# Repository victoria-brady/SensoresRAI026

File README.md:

# SensoresRAI026 — Array de sensores de proximidad para RAI

Firmware y herramientas del **array de sensores de distancia** del robot perro
cuadrúpedo **RAI** (ITBA, RAI 2026).

El sistema lee **4 sensores láser ToF VL53L0X** + **2 sensores ultrasónicos
HC-SR04** sobre un **Arduino GIGA R1 WiFi**, filtra las lecturas y emite las
distancias (en mm) por **USB Serial**. Una PC con el Arduino enchufado corre un
puente Python que reenvía esos datos por **UDP** al *brainstem* del robot, que
los usa para el reflejo de detección/frenado ante obstáculos.

```
   ┌──────────────┐   USB Serial    ┌─────────────────────────┐    UDP :43899   ┌────────────┐
   │ Arduino GIGA │  115200 baud    │ PC con el Arduino:       │   datagramas    │ brainstem  │
   │  R1 WiFi     │ ───────────────▶│ serial_to_udp_bridge.py │ ───────────────▶│ del robot  │
   │ (firmware)   │  CSV de 6 dist. │ (lee Serial, manda UDP) │                 │            │
   └──────────────┘                 └─────────────────────────┘                 └────────────┘
        ▲
   4× VL53L0X (I2C) + 2× HC-SR04 (interrupción)
```

---

## Versión activa

> **La versión activa y de referencia es [`src/object_detect_V3/`](src/object_detect_V3/).**

Es la última iteración (junio 2026) y la única con arquitectura **modular**
(drivers, filtro, scheduler y empaquetado en archivos separados). Las versiones
anteriores se conservan como histórico — ver [Historial de versiones](#historial-de-versiones).

> ⚠️ **Gap conocido de integración.** El firmware V3 emite el CSV *sin* el marco
> `S...E`, pero el puente `serial_to_udp_bridge.py` todavía descarta toda línea
> que no empiece con `S` y termine con `E` (protocolo de la V2). Tal cual están
> hoy, **V3 + bridge no se hablan**: el bridge filtra el 100% de los paquetes.
> Ver [Integración Serial → UDP](#integración-serial--udp).

---

## Hardware

| Componente            | Cantidad | Bus / Pines                                  |
|-----------------------|----------|----------------------------------------------|
| Arduino GIGA R1 WiFi  | 1        | Placa principal                              |
| VL53L0X (láser ToF)   | 4        | I2C @ 400 kHz · XSHUT en D2, D3, D4, D5      |
| HC-SR04 (ultrasónico) | 2        | TRIG D8 / ECHO D9 · TRIG D13 / ECHO D12      |

- Cada VL53L0X recibe una dirección I2C única en el arranque (`0x30`–`0x33`),
  encendiéndolos de a uno por su pin XSHUT.
- Los HC-SR04 se miden por **interrupción** sobre el pin ECHO (CHANGE), así el
  loop nunca se bloquea esperando el eco.
- El diseño de la placa (KiCad, 6 sensores) está en [`PCB/`](PCB/).

---

## Estructura del repositorio

```
src/
  object_detect_V3/        ← VERSIÓN ACTIVA (firmware modular)
  object_detect_V2/        firmware monolítico con WiFi/UDP opcional (histórico)
  object_detect_V1/        primer firmware monolítico, solo Serial (histórico)
  sensorsRAI_V1/           prototipo dual (2 VL + 1 US), bloqueante (histórico)
  sensorsRAI_V2/           duplicado de object_detect_V2 (artefacto de rename)
  sensorsRAI_BLW.ino/      prototipo por Bluetooth LE (histórico)
  sensorRAI_BLR.py         cliente Python del prototipo BLE (histórico)
  serial_to_udp_bridge.py  puente Serial → UDP para el brainstem
tests/                     sketches de validación de hardware (sensores sueltos)
PCB/                       proyecto KiCad de la placa (6 sensores)
docs/                      links a datasheets, Drive y planos de conexión
```

---

## Firmware activo: `object_detect_V3`

Arquitectura modular. Cada `.ino`/`.cpp` tiene una responsabilidad:

| Archivo                  | Responsabilidad                                                        |
|--------------------------|-----------------------------------------------------------------------|
| `object_detect_V3.ino`   | `setup()` + `loop()`; orquesta el ciclo de lectura vía scheduler       |
| `config.h`               | Toda la configuración: pines, direcciones I2C, Nº de sensores, límites |
| `VL53L0X.cpp/.h`         | Init secuencial con dirección I2C única + *watchdog* por sensor        |
| `HC-SR04.cpp/.h`         | Disparo no bloqueante + medición del eco por ISR                       |
| `filter.cpp/.h`          | Filtro de media con rechazo por desviación estándar                    |
| `PacketPush.cpp/.h`      | `struct SensorPacket` + envío del CSV por Serial                       |
| `my_timer.cpp/.h`        | Scheduler cooperativo genérico (`runTaskPeriodically`)                 |

### Cómo funciona

Cada `LOOP_MS` (50 ms ≈ 20 Hz) el scheduler ejecuta `procesarSensores()`, que:

1. Dispara los dos ultrasonidos (el eco lo captura la ISR en segundo plano).
2. Lee y filtra los 4 láseres.
3. Lee y filtra los 2 ultrasonidos (datos del eco del ciclo anterior).
4. Envía el paquete por Serial.

**Filtro (`filter.cpp`):** mantiene un buffer circular de `FILTER_N` muestras por
sensor, ignora los ceros (lecturas inválidas) y devuelve la **media**. Si la
**desviación estándar** del buffer supera `MAX_STD_DEV_*` (lecturas caóticas /
pico de ruido), amortigua a `0` en vez de propagar basura.

**Watchdog (`VL53L0X.cpp`):** un sensor que entrega `MAX_FALLOS` lecturas
inválidas seguidas se apaga y reinicia solo, sin trabar al resto del array.

### Parámetros (`config.h`)

| Parámetro                  | Valor    | Significado                                       |
|----------------------------|----------|---------------------------------------------------|
| `LOOP_MS`                  | 50       | Período del ciclo (~20 Hz)                         |
| `FILTER_N`                 | 5        | Muestras del filtro por sensor                     |
| `MAX_FALLOS`               | 5        | Fallos seguidos antes de reiniciar un sensor       |
| `NUM_VL` / `NUM_US`        | 4 / 2    | Cantidad de láseres / ultrasonidos                 |
| `MAX_STD_DEV_VL` / `_US`   | 500 / 500| Desvío estándar máx. tolerado (mm) antes de cortar |
| `VL_MIN`..`VL_MAX`         | 0..9000  | Rango válido del láser (`VL_ERR` = 8190)           |
| `US_MIN`..`US_MAX`         | 0..9000  | Rango válido del ultrasonido                        |

### Formato de salida

Línea de texto ASCII por ciclo: **6 enteros (mm) separados por coma**, terminada
en `\n`, a **115200 baud**. `0` = sin lectura válida ese ciclo.

El orden de los campos **no** es FL,FC,FR,... sino el que define
[`PacketPush.cpp`](src/object_detect_V3/PacketPush.cpp):

| Campo CSV | Fuente  | Posición física              |
|-----------|---------|------------------------------|
| 1         | `vl[2]` | **BR** — atrás-derecha       |
| 2         | `us[0]` | **FC** — adelante-centro     |
| 3         | `vl[3]` | **BL** — atrás-izquierda     |
| 4         | `vl[1]` | **FR** — adelante-derecha    |
| 5         | `us[1]` | **BC** — atrás-centro        |
| 6         | `vl[0]` | **FL** — adelante-izquierda  |

Ejemplo: `342,654,0,891,0,1205`

### Compilar y cargar

1. Arduino IDE con soporte para **Arduino GIGA R1** (core *Arduino Mbed OS GIGA*).
2. Instalar la librería **Adafruit_VL53L0X** (Library Manager).
3. Abrir `src/object_detect_V3/object_detect_V3.ino` (el IDE toma todos los `.cpp/.h`
   de la carpeta) y cargar a la placa.
4. Verificar las lecturas en el Monitor Serie a **115200 baud**.

---

## Integración Serial → UDP

[`src/serial_to_udp_bridge.py`](src/serial_to_udp_bridge.py) corre en la PC que
tiene el Arduino conectado por USB: lee las líneas del Serial y las reenvía como
datagramas UDP al *brainstem* (puerto **43899** = `kSensorUdpPort`). Así el
Arduino no necesita WiFi.

```bash
pip install pyserial

# Ver puertos disponibles
python src/serial_to_udp_bridge.py --list

# Reenviar COM5 → brainstem en otra PC de la red del robot
python src/serial_to_udp_bridge.py --port COM5 --dest-ip 192.168.1.50
```

| Flag          | Default     | Descripción                                       |
|---------------|-------------|---------------------------------------------------|
| `--list`      | —           | Lista los puertos serie y sale                    |
| `--port`      | (requerido) | Puerto del Arduino (`COM5`, `/dev/ttyACM0`, …)    |
| `--baud`      | 115200      | Debe coincidir con `Serial.begin()` del firmware  |
| `--dest-ip`   | 127.0.0.1   | IP de la PC que corre el brainstem                |
| `--dest-port` | 43899       | Puerto UDP del brainstem                          |
| `--echo`      | —           | Imprime cada paquete reenviado (debug)            |

> **Windows:** el puerto COM es exclusivo. Cerrá el Monitor Serie del Arduino IDE
> antes de correr el bridge o vas a ver *"Access is denied"*.

> ⚠️ **Para que V3 funcione con el bridge** hay que cerrar el gap del marco `S...E`:
> o bien **re-activar** el frame en `PacketPush.cpp` (las líneas `Serial.print('S')`
> / `Serial.println('E')` están comentadas), o bien **relajar** `looks_valid()` en
> el bridge para que acepte CSV pelado. Hoy el bridge espera el formato de la V2.

---

## Historial de versiones

| Versión                | Sensores        | Transporte            | Filtro            | Estado                              |
|------------------------|-----------------|-----------------------|-------------------|-------------------------------------|
| **`object_detect_V3`** | 4 VL + 2 US     | USB Serial            | media + σ (std)   | **Activa** (modular)                |
| `object_detect_V2`     | 4 VL + 2 US     | Serial + WiFi/UDP opc.| mediana (N=3)     | Histórico — compatible con el bridge |
| `object_detect_V1`     | 4 VL + 2 US     | USB Serial            | mediana (N=5)     | Histórico                            |
| `sensorsRAI_V1`        | 2 VL + 1 US     | Serial (texto legible)| —                 | Prototipo bloqueante                 |
| `sensorsRAI_BLW` + `sensorRAI_BLR.py` | 2 VL + 1 US | Bluetooth LE | — | Prototipo abandonado                 |
| `sensorsRAI_V2`        | —               | —                     | —                 | Duplicado de V2 (artefacto de rename)|

- **V1 → V2:** se agregó WiFi/UDP opcional (`ENABLE_WIFI`), modo `HIGH_SPEED` del
  láser, y se bajó la mediana de 5 a 3 muestras (menor latencia ante un obstáculo
  súbito). La V2 mantiene el protocolo `S...E` que el bridge espera.
- **V2 → V3:** refactor a módulos, scheduler cooperativo, y cambio de filtro
  (mediana → media con rechazo por desviación estándar). Se quitó el WiFi: V3 es
  solo Serial (la salida a UDP queda a cargo del bridge en la PC).

---

## Tests (`tests/`)

Sketches independientes para validar hardware suelto antes de integrar:

- `HCSR04_single/` — un único HC-SR04.
- `vl53l0x_dual/` — dos VL53L0X (ejemplo Adafruit de direccionamiento I2C).
- `test4VL/` — driver propio para N VL53L0X. *Nota:* `config.h` declara
  `NUMSENSORS 4` pero `XSHUT_PINS` solo lista 2 pines `{5, 4}` — completar antes
  de usar con 4 sensores.

---

## Documentación

- [`docs/Arduino Giga/`](docs/Arduino%20Giga/) — datasheet y manual del GIGA R1.
- [`docs/Sensores/`](docs/Sensores/) — planos de conexión y carpeta de Drive.
- [`PCB/`](PCB/) — proyecto KiCad de la placa de 6 sensores.

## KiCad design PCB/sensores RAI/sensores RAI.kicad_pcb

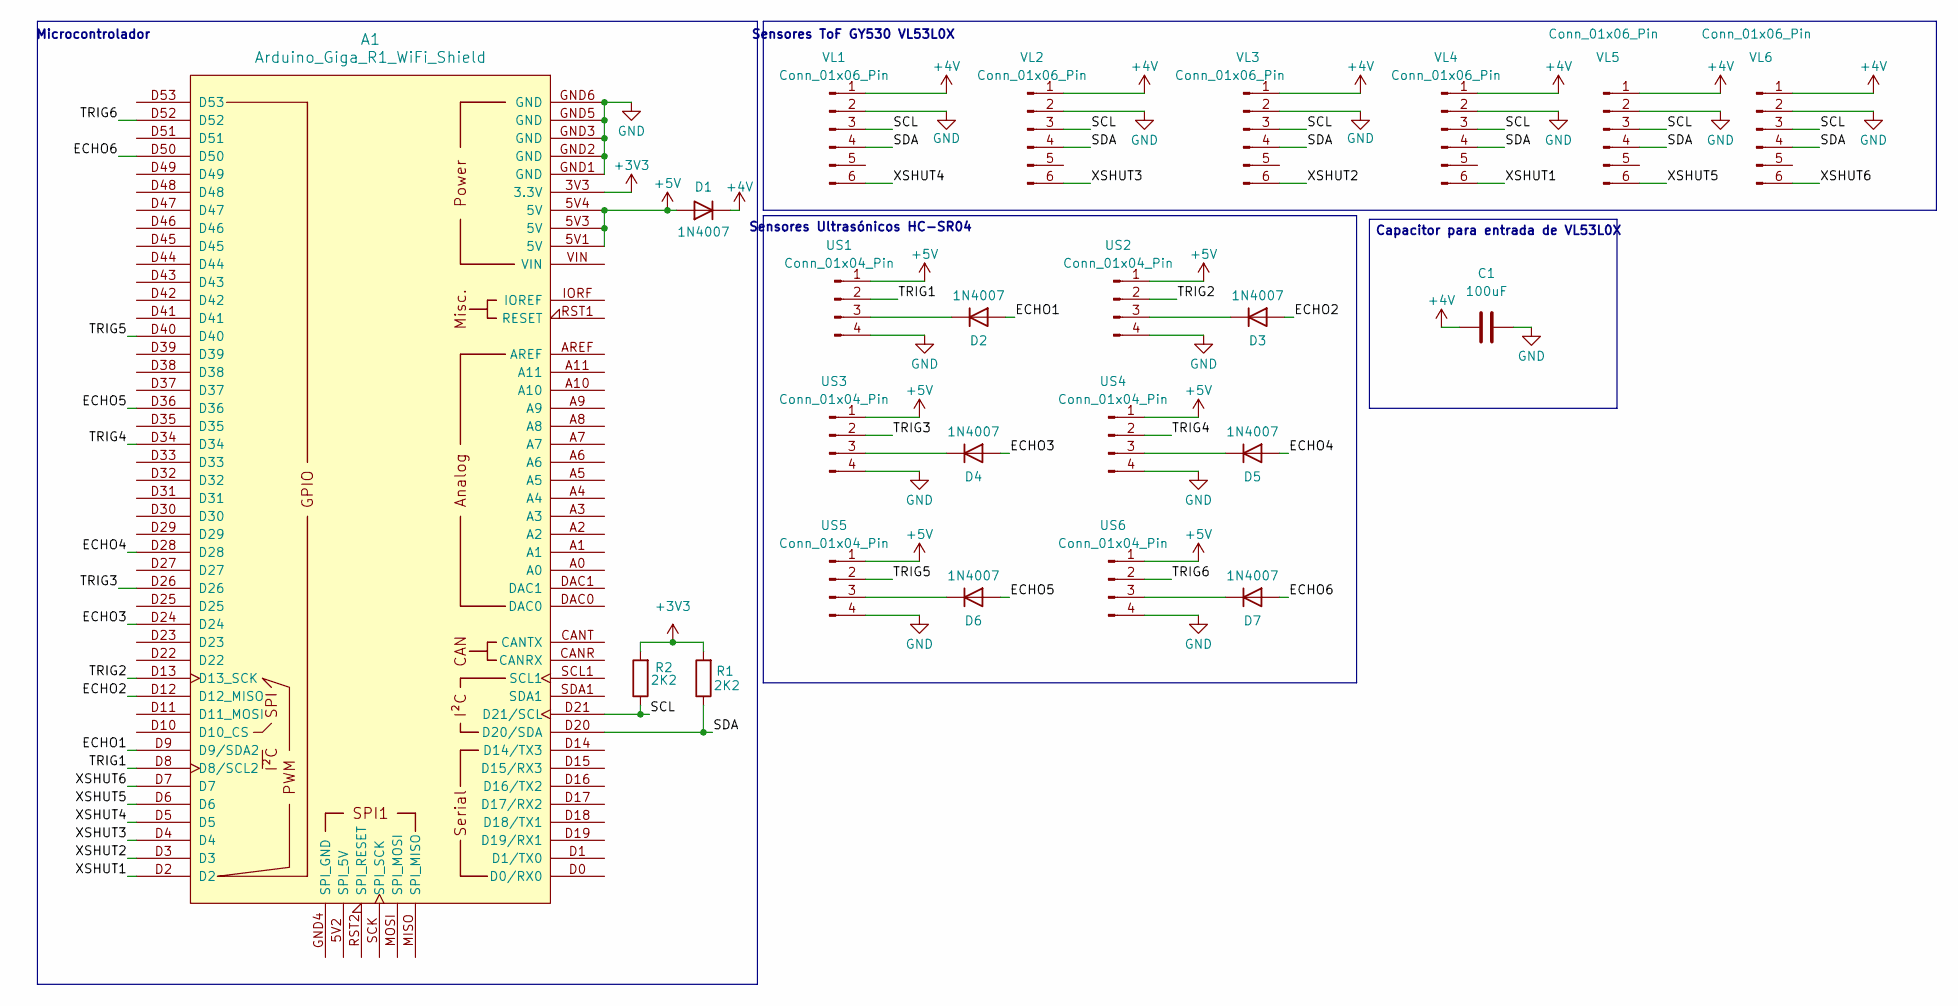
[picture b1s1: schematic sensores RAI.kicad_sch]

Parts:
A1: Arduino_Giga_R1_WiFi_Shield; Arduino_Giga_R1_WiFi_Shield_sin_nada_en_medio
C1: 100uF; CP_Radial_Tantal_D6.0mm_P2.50mm
D1, D2, D3, D4, D5, D6, D7: 1N4007; D_DO-41_SOD81_P10.16mm_Horizontal
R1, R2: 2K2; R_Axial_DIN0207_L6.3mm_D2.5mm_P10.16mm_Horizontal
US1, US2, US3, US4, US5, US6: Conn_01x04_Pin; Molex_KK-254_AE-6410-04A_1x04_P2.54mm_Vertical
VL1, VL2, VL3, VL4, VL5, VL6: Conn_01x06_Pin; Molex_KK-254_AE-6410-06A_1x06_P2.54mm_Vertical

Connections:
+3V3: A1.3V3 (3.3V), R1.2, R2.2
+4V: C1.1, D1.1 (K), VL1.1, VL2.1, VL3.1, VL4.1, VL5.1, VL6.1
+5V: A1.5V1 (5V), A1.5V3 (5V), A1.5V4 (5V), D1.2 (A), US1.1, US2.1, US3.1, US4.1, US5.1, US6.1
/ECHO1: A1.D9 (D9/SDA2), D2.2 (A)
/ECHO2: A1.D12 (D12_MISO), D3.2 (A)
/ECHO3: A1.D24, D4.2 (A)
/ECHO4: A1.D28, D5.2 (A)
/ECHO5: A1.D36, D6.2 (A)
/ECHO6: A1.D50, D7.2 (A)
/SCL: A1.D21 (D21/SCL), R2.1, VL1.3, VL2.3, VL3.3, VL4.3, VL5.3, VL6.3
/SDA: A1.D20 (D20/SDA), R1.1, VL1.4, VL2.4, VL3.4, VL4.4, VL5.4, VL6.4
/TRIG1: A1.D8 (D8/SCL2), US1.2
/TRIG2: A1.D13 (D13_SCK), US2.2
/TRIG3: A1.D26, US3.2
/TRIG4: A1.D34, US4.2
/TRIG5: A1.D40, US5.2
/TRIG6: A1.D52, US6.2
/XSHUT1: A1.D2, VL4.6
/XSHUT2: A1.D3, VL3.6
/XSHUT3: A1.D4, VL2.6
/XSHUT4: A1.D5, VL1.6
/XSHUT5: A1.D6, VL5.6
/XSHUT6: A1.D7, VL6.6
GND: A1.GND1 (GND), A1.GND2 (GND), A1.GND3 (GND), A1.GND5 (GND), A1.GND6 (GND), C1.2, US1.4, US2.4, US3.4, US4.4, US5.4, US6.4, VL1.2, VL2.2, VL3.2, VL4.2, VL5.2, VL6.2
unnamed: D2.1 (K), US1.3
unnamed: D3.1 (K), US2.3
unnamed: D4.1 (K), US3.3
unnamed: D5.1 (K), US4.3
unnamed: D6.1 (K), US5.3
unnamed: D7.1 (K), US6.3

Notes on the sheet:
Sensores ToF GY530 VL53L0X
Sensores Ultrasónicos HC-SR04
Capacitor para entrada de VL53L0X
Microcontrolador

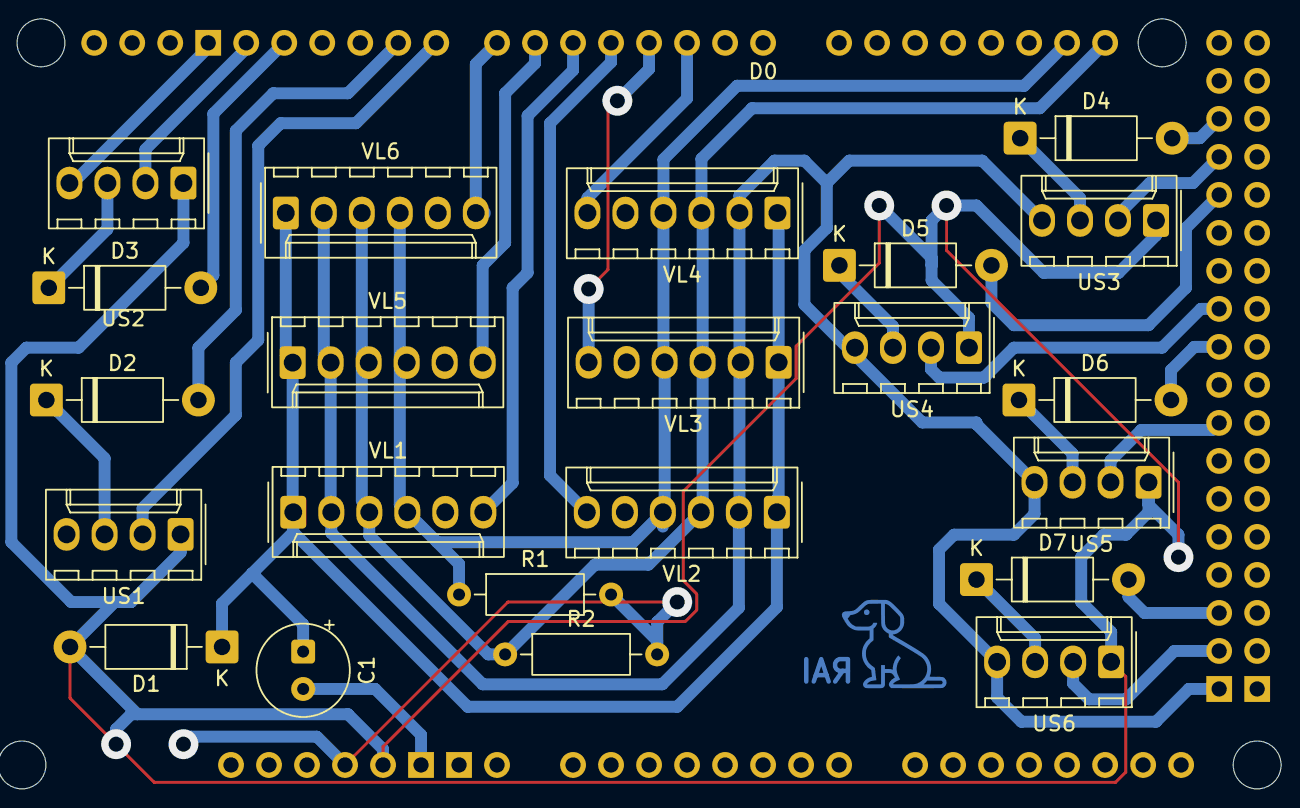
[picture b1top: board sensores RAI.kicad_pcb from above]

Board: 2 copper layers, 23 parts (0 on the bottom side), 30 nets.

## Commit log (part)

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2026-05-04 codigo de sensores
2026-05-04 prueba de sensores
2026-05-05 Organice un poco y agregue links de info
2026-05-15 Ya funcionan 2 vl y 1 ultrasonico juntos
2026-05-17 Agregue y actualice codigos de prueba.
2026-05-17 Borre codigo extra
2026-05-17 Subí esquemático conexiones dos vl + un ultrasonico
2026-05-18 Elimine codigo extra
2026-05-18 Codigo para 4 vl y 2 ultras. Funciona.
2026-05-18 Subi codigos de bluetooth para leer distancias remotamente. Funcionan.
2026-05-23 Placa lista para imprimir.
2026-05-26 Agregué imagen de conexion 6 sensores
2026-05-26 Added final sensor array code
    Lee los vl y ultrasónicos, envía una línea al jetson (z1, z2, z3, z4, z5, z6), donde cada posición representa la zona y el valor (0, 1 o 2) representa la distancia a la que se encuentre el objeto en 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
2026-05-26 Add final sensor array code
2026-05-26 Delete src/object_detect_RAI/sensores_RAI_v2/sensores_RAI directory
    extra
2026-05-26 Update README with corrected sensor descriptions
2026-05-28 object_detect_3
    Esta versión registra las lecturas de los sensores con algunos filtros pero devuelve los datos crudos, sin procesarlos. devuelve un vector S vl1 vl2 vl3 vl4 us1 us2 E. VL1: izquierda adelante. VL2: d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
2026-05-29 test4VL added
2026-05-29 Update sensorsRAI_V2.ino
    Cambie pines
2026-05-29 Cambie de lugar
2026-05-29 cambiamos codigo object_detect
2026-05-29 Cambie nombres
2026-05-29 Update object_detect_V2.ino to enhance WiFi configuration and UDP packet handling
2026-05-29 cambiamos comentarios posicion lectura
2026-05-29 Add serial_to_udp_bridge.py for bridging Serial to UDP communication
2026-05-29 Object Detect V3
2026-06-01 colgue en poner esto que cambie el viernes pasado al final
2026-06-01 Improve serial_to_udp_bridge.py documentation and error handling
2026-06-01 cambio de pines
2026-06-01 Reduce median filter samples from 5 to 3 for improved obstacle response time and update loop timing for better latency management.
2026-06-01 hola soy feli
2026-06-16 whiskers
2026-06-22 kicad placa 12 sensores
